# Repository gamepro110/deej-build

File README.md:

# deej-build

| dir | what |
| --- | --- |
| [pcb](<./pcb/>) | pcb design files |
| [µ code](<./µ code/>) | code for the µ (micro) controller |

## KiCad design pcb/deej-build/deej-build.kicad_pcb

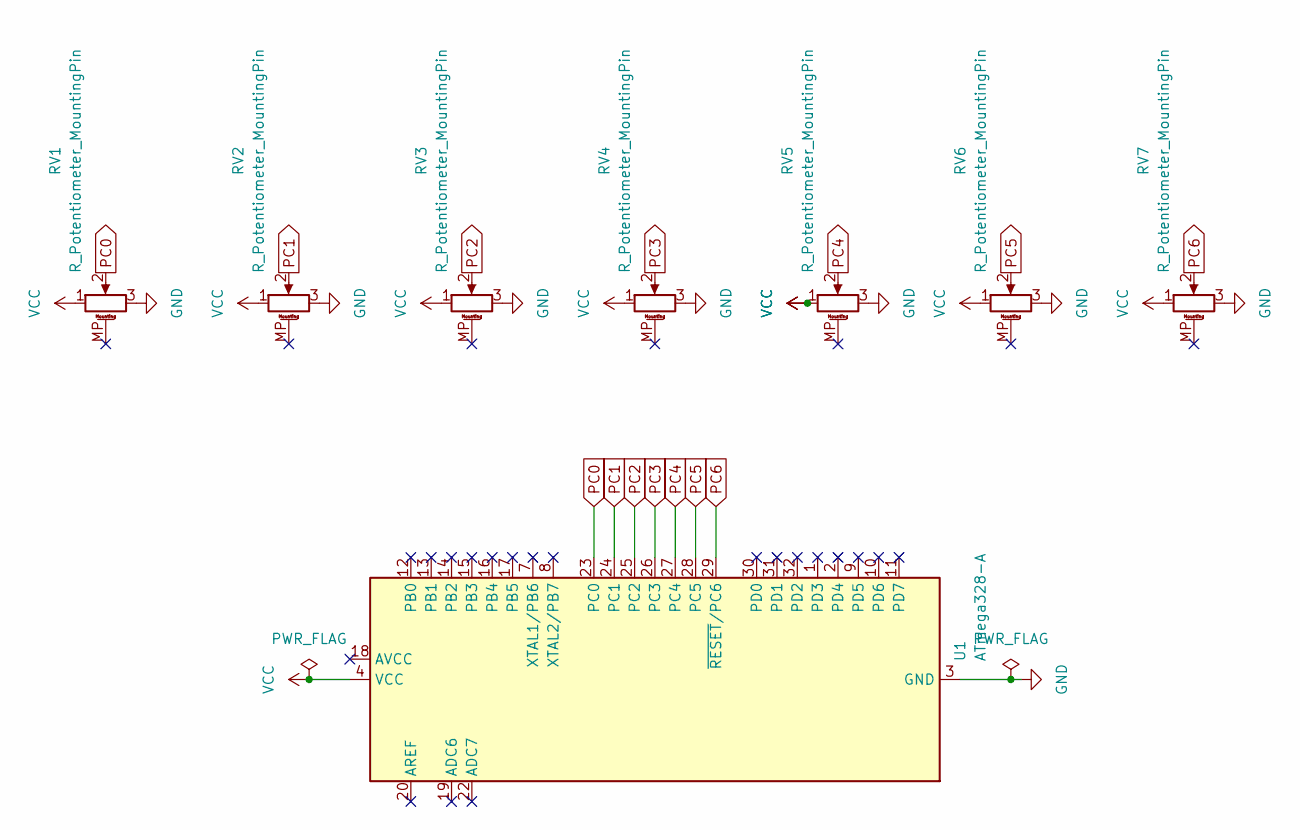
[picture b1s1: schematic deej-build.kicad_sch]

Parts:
RV1, RV2, RV3, RV4, RV5, RV6, RV7: R_Potentiometer_MountingPin; Potentiometer_Bourns_PTA6043_Single_Slide
U1: ATmega328-A; TQFP-32_7x7mm_P0.8mm

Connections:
GND: RV1.3, RV2.3, RV3.3, RV4.3, RV5.3, RV6.3, RV7.3, U1.3 (GND), U1.5 (GND), U1.21 (GND)
PC0: RV1.2, U1.23 (PC0)
PC1: RV2.2, U1.24 (PC1)
PC2: RV3.2, U1.25 (PC2)
PC3: RV4.2, U1.26 (PC3)
PC4: RV5.2, U1.27 (PC4)
PC5: RV6.2, U1.28 (PC5)
PC6: RV7.2, U1.29 (~RESET/PC6)
VCC: RV1.1, RV2.1, RV3.1, RV4.1, RV5.1, RV6.1, RV7.1, U1.4 (VCC), U1.6 (VCC)

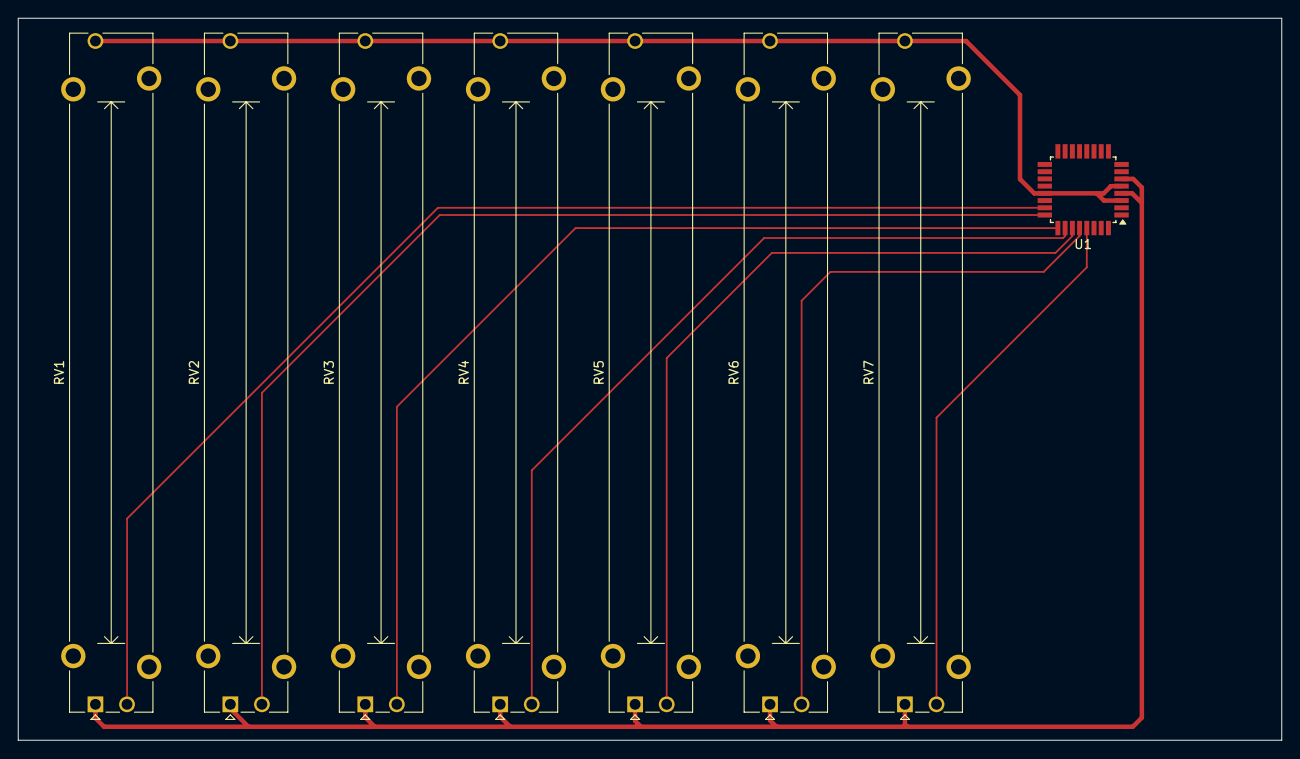
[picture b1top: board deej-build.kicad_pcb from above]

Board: 2 copper layers, 140.0 x 80.0 mm, 8 parts (0 on the bottom side), 9 nets.
